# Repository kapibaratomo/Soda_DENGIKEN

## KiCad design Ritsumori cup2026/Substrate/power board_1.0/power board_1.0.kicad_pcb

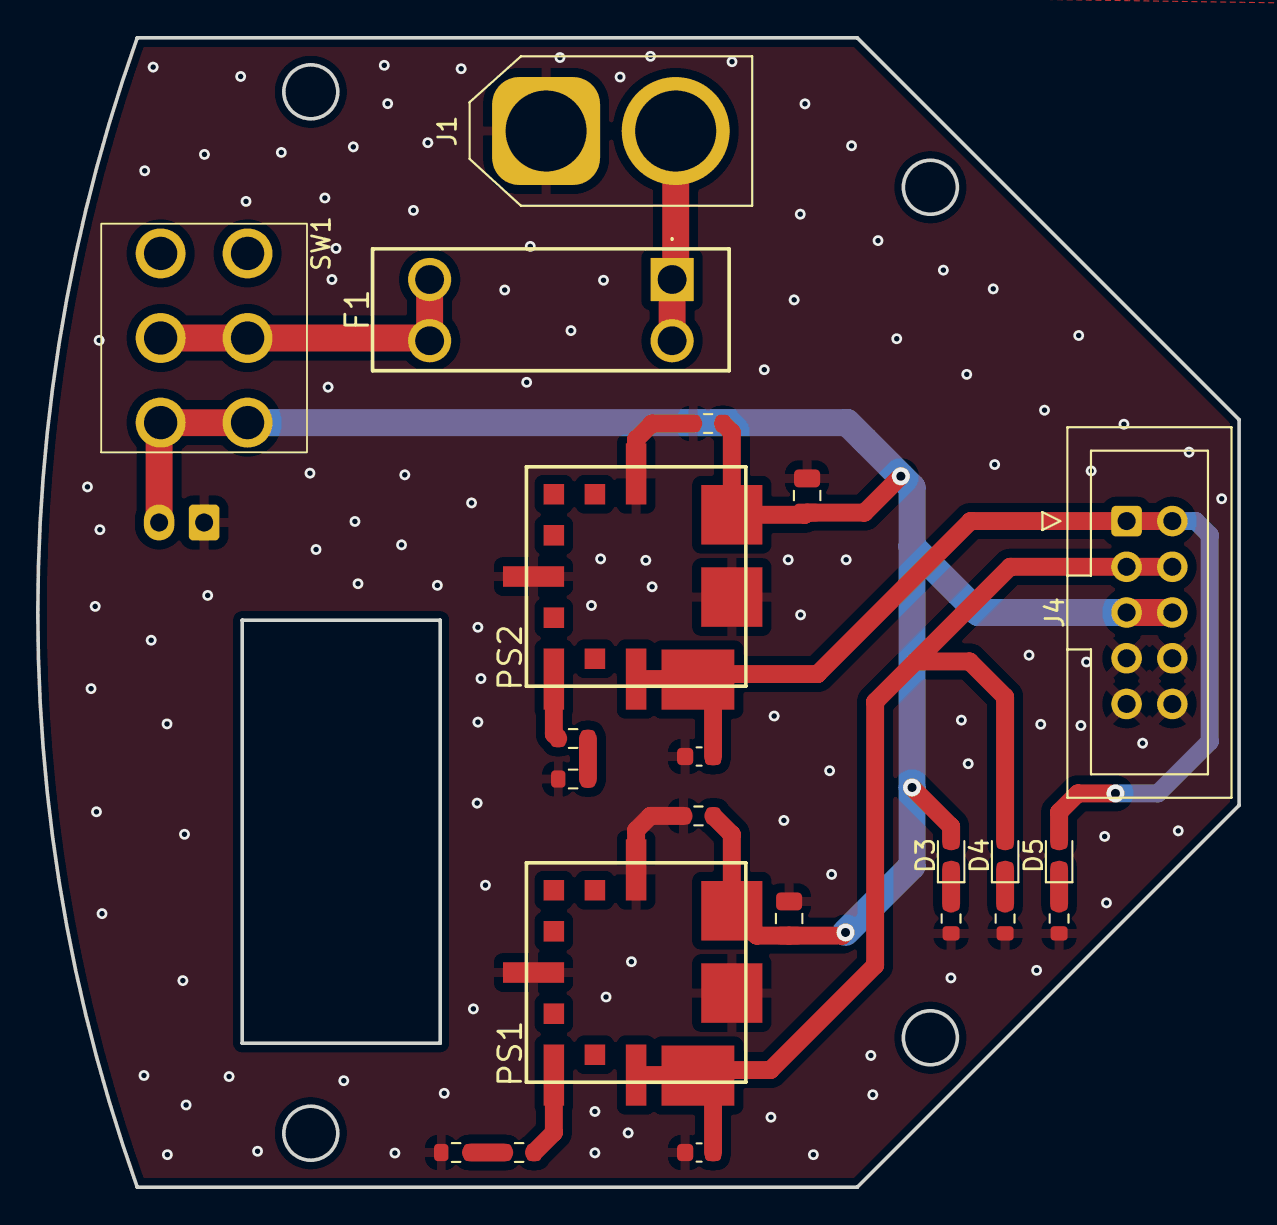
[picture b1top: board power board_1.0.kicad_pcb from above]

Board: 2 copper layers, 66.7 x 63.9 mm, 23 parts (1 on the bottom side), 13 nets.

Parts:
C1, C3: 22u; C_0805_2012Metric
C2, C4: 10u; C_0603_1608Metric
D3, D4, D5: LED; LED_0603_1608Metric
F1: Fuse; 355715
J1: Conn_01x02_Socket; AMASS_XT60-M_1x02_P7.20mm_Vertical
J2: 電圧計; JST_XH_B2B-XH-A_1x02_P2.50mm_Vertical
J4: Conn_02x05_Counter_Clockwise; IDC-Header_2x05_P2.54mm_Vertical
PS1, PS2: OKL-T_6-W12N-C; OKLT6W12NC
R1, R9: 680; R_0603_1608Metric
R2: 200; R_0603_1608Metric
R3: 75; R_0603_1608Metric
R4, R7: 20k; R_0603_1608Metric
R5: 1k; R_0603_1608Metric
R6: 330; R_0603_1608Metric
R8: 1.5k; R_0603_1608Metric
SW1: SW_Push_DPDT; Toggle

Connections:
+3.3V: C4.1, D5.2 (A), J4.1, J4.2, PS2.4 (VOUT), PS2.5 (SENSE)
+5V: C2.1, D4.2 (A), J4.3, J4.4, PS1.4 (VOUT), PS1.5 (SENSE)
+12V: C1.1, C3.1, D3.2 (A), J2.2, J4.5, J4.6, PS1.2 (VIN), PS2.2 (VIN), R4.1, R7.1, SW1.1 (A), SW1.4 (A)
GND: C1.2, C2.2, C3.2, C4.2, J1.1, J2.1, J4.7, J4.8, J4.9, J4.10, PS1.1 (ON/OFF_CONTROL), PS1.3 (GROUND_1), PS1.7 (GROUND_2), PS2.1 (ON/OFF_CONTROL), PS2.3 (GROUND_1), PS2.7 (GROUND_2), R1.1, R2.1, R3.1, R4.2, R6.2, R7.2, R9.2
unnamed: D3.1 (K), R1.2
unnamed: D4.1 (K), R2.2
unnamed: D5.1 (K), R3.2
unnamed: F1.2, SW1.2 (B), SW1.5 (B)
unnamed: F1.1, J1.2
unnamed: PS1.6 (TRIM), R5.1
unnamed: PS2.6 (TRIM), R8.1
unnamed: R5.2, R6.1
unnamed: R8.2, R9.1

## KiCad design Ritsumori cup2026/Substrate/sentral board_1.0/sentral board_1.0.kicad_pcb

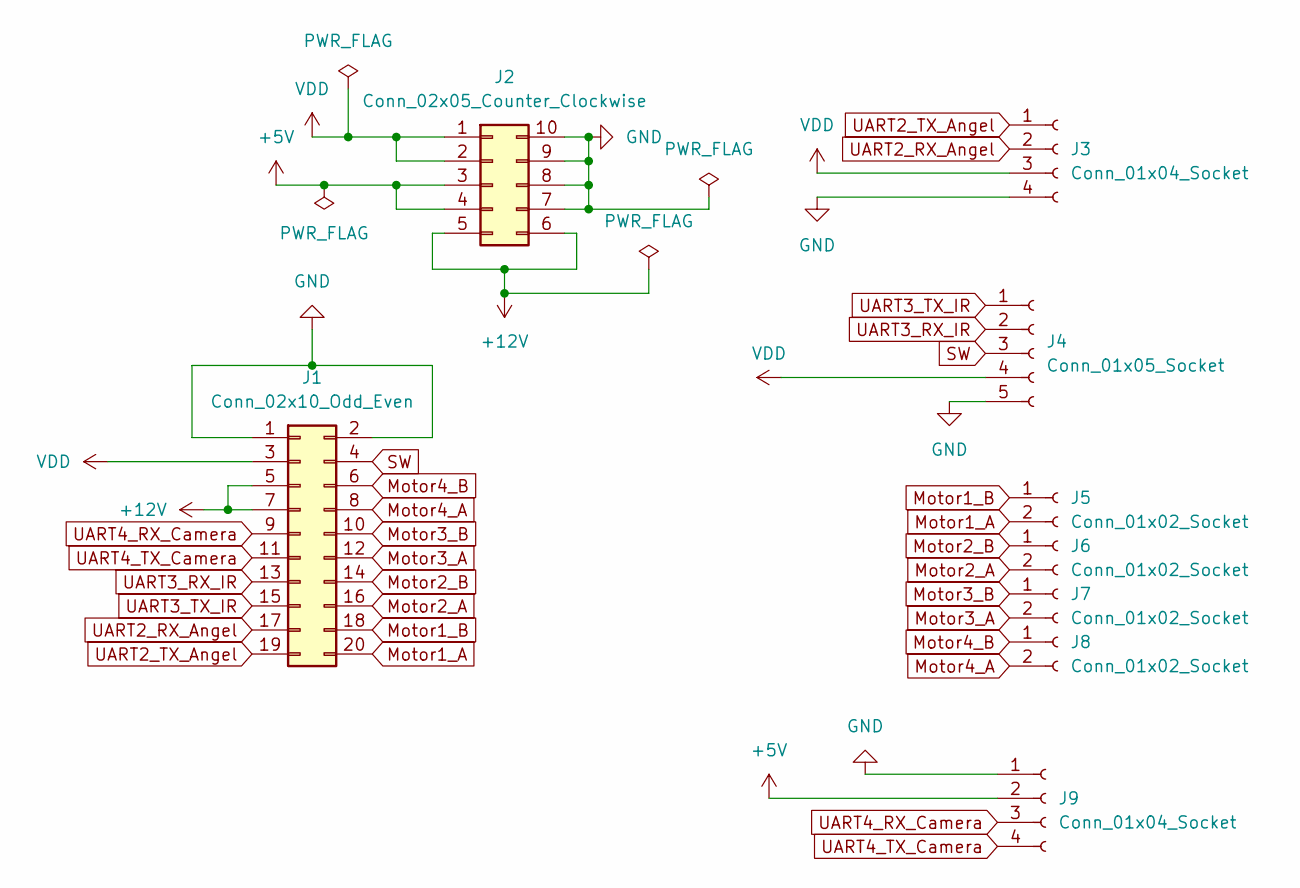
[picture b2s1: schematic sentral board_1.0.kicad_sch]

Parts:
J1: Conn_02x10_Odd_Even; IDC-Header_2x10_P2.54mm_Vertical
J2: Conn_02x05_Counter_Clockwise; IDC-Header_2x05_P2.54mm_Vertical
J3, J9: Conn_01x04_Socket; JST_XH_B4B-XH-A_1x04_P2.50mm_Vertical
J4: Conn_01x05_Socket; JST_XH_B5B-XH-A_1x05_P2.50mm_Vertical
J5, J6, J7, J8: Conn_01x02_Socket; JST_XH_S2B-XH-A_1x02_P2.50mm_Horizontal

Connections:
+5V: J2.3, J2.4, J9.2
+12V: J1.5, J1.7, J2.5, J2.6
GND: J1.1, J1.2, J2.7, J2.8, J2.9, J2.10, J3.4, J4.5, J9.1
Motor1_A: J1.20, J5.2
Motor1_B: J1.18, J5.1
Motor2_A: J1.16, J6.2
Motor2_B: J1.14, J6.1
Motor3_A: J1.12, J7.2
Motor3_B: J1.10, J7.1
Motor4_A: J1.8, J8.2
Motor4_B: J1.6, J8.1
SW: J1.4, J4.3
UART2_RX_Angel: J1.17, J3.2
UART2_TX_Angel: J1.19, J3.1
UART3_RX_IR: J1.13, J4.2
UART3_TX_IR: J1.15, J4.1
UART4_RX_Camera: J1.9, J9.3
UART4_TX_Camera: J1.11, J9.4
VDD: J1.3, J2.1, J2.2, J3.3, J4.4

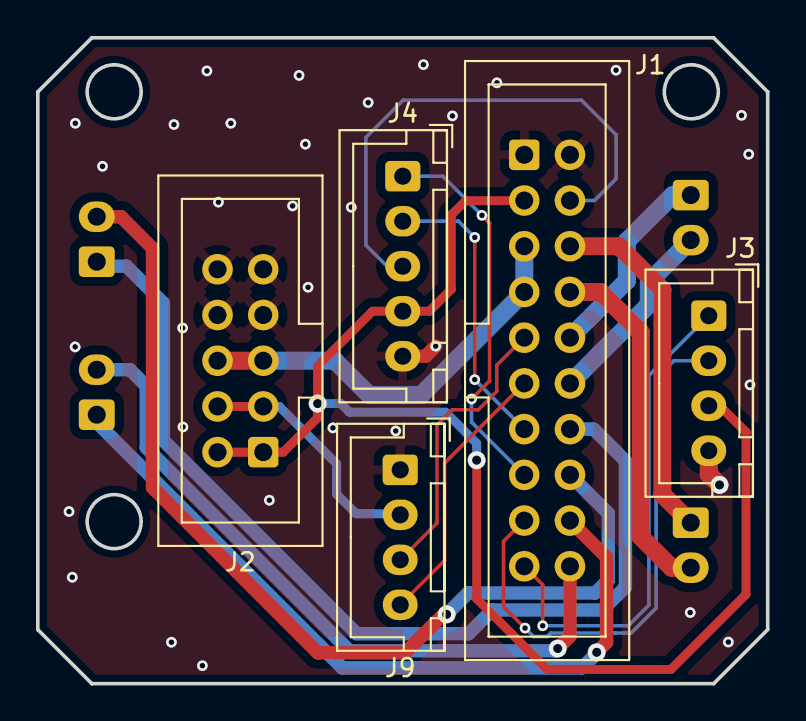
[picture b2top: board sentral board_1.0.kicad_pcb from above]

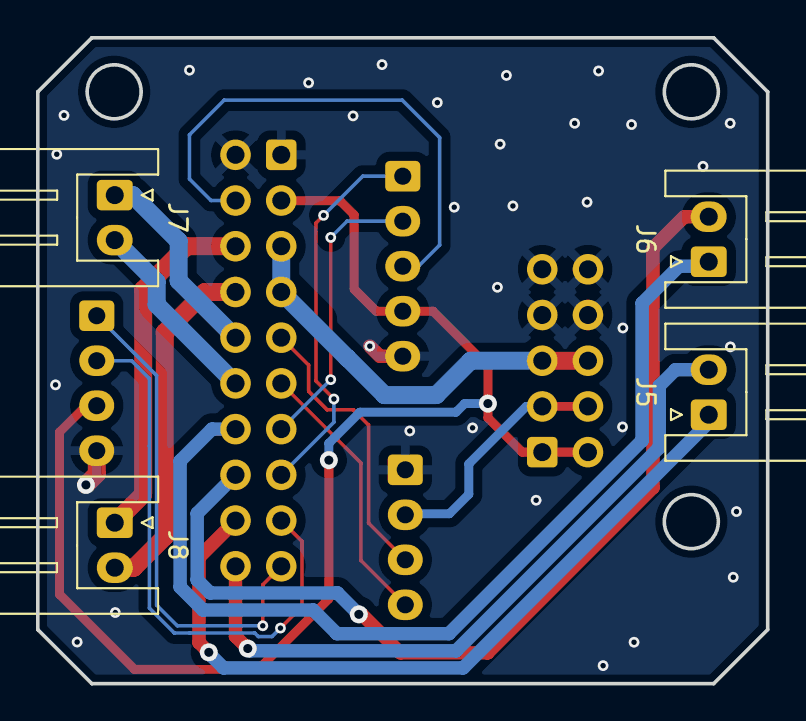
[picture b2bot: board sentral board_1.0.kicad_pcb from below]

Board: 2 copper layers, 40.6 x 35.9 mm, 9 parts (4 on the bottom side), 19 nets.
